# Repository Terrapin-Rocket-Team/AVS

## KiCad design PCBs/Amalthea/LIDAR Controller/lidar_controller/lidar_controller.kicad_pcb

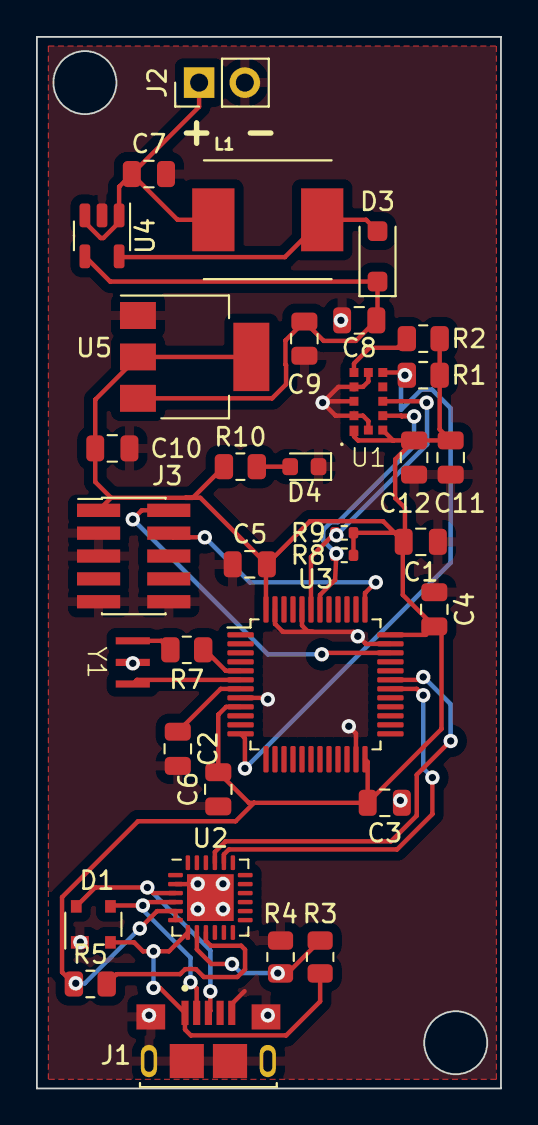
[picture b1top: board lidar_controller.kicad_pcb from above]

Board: 2 copper layers, 25.8 x 58.4 mm, 34 parts (0 on the bottom side), 23 nets.

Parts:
C1, C11: 4.7uF; C_0805_2012Metric
C2, C3, C4, C5, C6, C9, C12: 100nF; C_0805_2012Metric
C7, C8, C10: 10uF; C_0805_2012Metric
D1: SP0503BAHT; SOT-143
D3: D_Schottky; D_SOD-123F
D4: LED; D_0603_1608Metric
J1: 10118193-0001LF; AMPHENOL_10118193-0001LF
J2: Conn_01x02_Pin; PinHeader_1x02_P2.54mm_Vertical
J3: Conn_ARM_JTAG_SWD_10; PinHeader_2x05_P1.27mm_Vertical_SMD
L1: 10uH; IND_ASPI-0630LR-100M-T15
R1, R2: 10k; R_0805_2012Metric
R3: 22.1k; R_0805_2012Metric
R4: 47.5k; R_0805_2012Metric
R5: 1k; R_0805_2012Metric
R7: 1M; R_0805_2012Metric
R8, R9: 4.7k; R_0402_1005Metric
R10: 500; R_0805_2012Metric
U1: VL53L3CX
U2: CP2102N-Axx-xQFN24; QFN-24-1EP_4x4mm_P0.5mm_EP2.6x2.6mm
U3: STM32F103C8Tx; LQFP-48_7x7mm_P0.5mm
U4: RP400N501A-TR-FE; SOT-23-5
U5: LDL1117S33R; SOT-223
Y1: Resonator; JGC42-8828A_CSTNE10M0G550000R0

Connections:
+3V3: C1.2, C3.2, C4.2, C5.2, C6.2, C10.2, C11.2, C12.2, J3.1 (VTref), R1.1, R2.2, R5.1, R8.2, R9.2, R10.1, U1.1 (AVDDVCSEL), U1.11 (AVDD), U2.5 (VIO), U2.6 (VDD), U3.9 (VDDA), U3.24 (VDD), U3.36 (VDD), U3.48 (VDD), U5.2 (VOUT), U5.4 (VOUT)
+5V: C8.1, C9.1, D3.1 (K), U4.4 (VOUT), U5.3 (VIN)
/LIDAR/INT: R1.2, U1.7 (GPIO1), U3.12 (PA2)
/LIDAR/SCL: R8.1, U1.10 (SCL), U3.42 (PB6)
/LIDAR/SDA: R9.1, U1.9 (SDA), U3.43 (PB7)
/Regulator/VIN: C7.1, J2.1, L1.1, U4.1 (CE), U4.3 (VIN)
/STM32F103/M_RX: U2.21 (TXD), U3.31 (PA10)
/STM32F103/M_TX: U2.20 (RXD), U3.30 (PA9)
/STM32F103/SWCLK: J3.4 (SWDCLK/TCK), U3.37 (PA14)
/STM32F103/SWDIO: J3.2 (SWDIO/TMS), U3.34 (PA13)
GND: C1.1, C2.2, C3.1, C4.1, C5.1, C6.1, C7.2, C8.2, C9.2, C10.1, C11.1, C12.1, D1.1 (A), D4.1 (K), J1.5 (GND), J1.S1 (SHIELD), J1.S2 (SHIELD), J1.S3 (SHIELD), J1.S4 (SHIELD), J1.S5 (SHIELD), J1.S6 (SHIELD), J2.2, J3.3 (GND), J3.5 (GND), J3.9 (GNDDetect), J3.10 (~RESET), R4.1, U1.2 (AVSSVCSEL), U1.3 (GND), U1.4 (GND2), U1.6 (GND3), U1.12 (GND4), U2.2 (GND), U2.25 (GND), U3.8 (VSSA), U3.23 (VSS), U3.35 (VSS), U3.44 (BOOT0), U3.47 (VSS), U4.2 (GND), U5.1 (GND), Y1.2
unnamed: D3.2 (A), L1.2, U4.5 (LX)
unnamed: D4.2 (A), R10.2
unnamed: D1.4 (K), J1.3 (D+), U2.3 (D+)
unnamed: D1.3 (K), J1.2 (D-), U2.4 (D-)
unnamed: D1.2 (K), J1.1 (VUSB), R3.2, U2.7 (VREGIN)
unnamed: R7.2, Y1.1
unnamed: R2.1, U1.5 (XSHUT)
unnamed: R3.1, R4.2, U2.8 (VBUS)
unnamed: R5.2, U2.9 (~RST)
unnamed: C2.1, U3.7 (NRST)
unnamed: R7.1, U3.5 (PD0)
unnamed: U3.6 (PD1), Y1.3

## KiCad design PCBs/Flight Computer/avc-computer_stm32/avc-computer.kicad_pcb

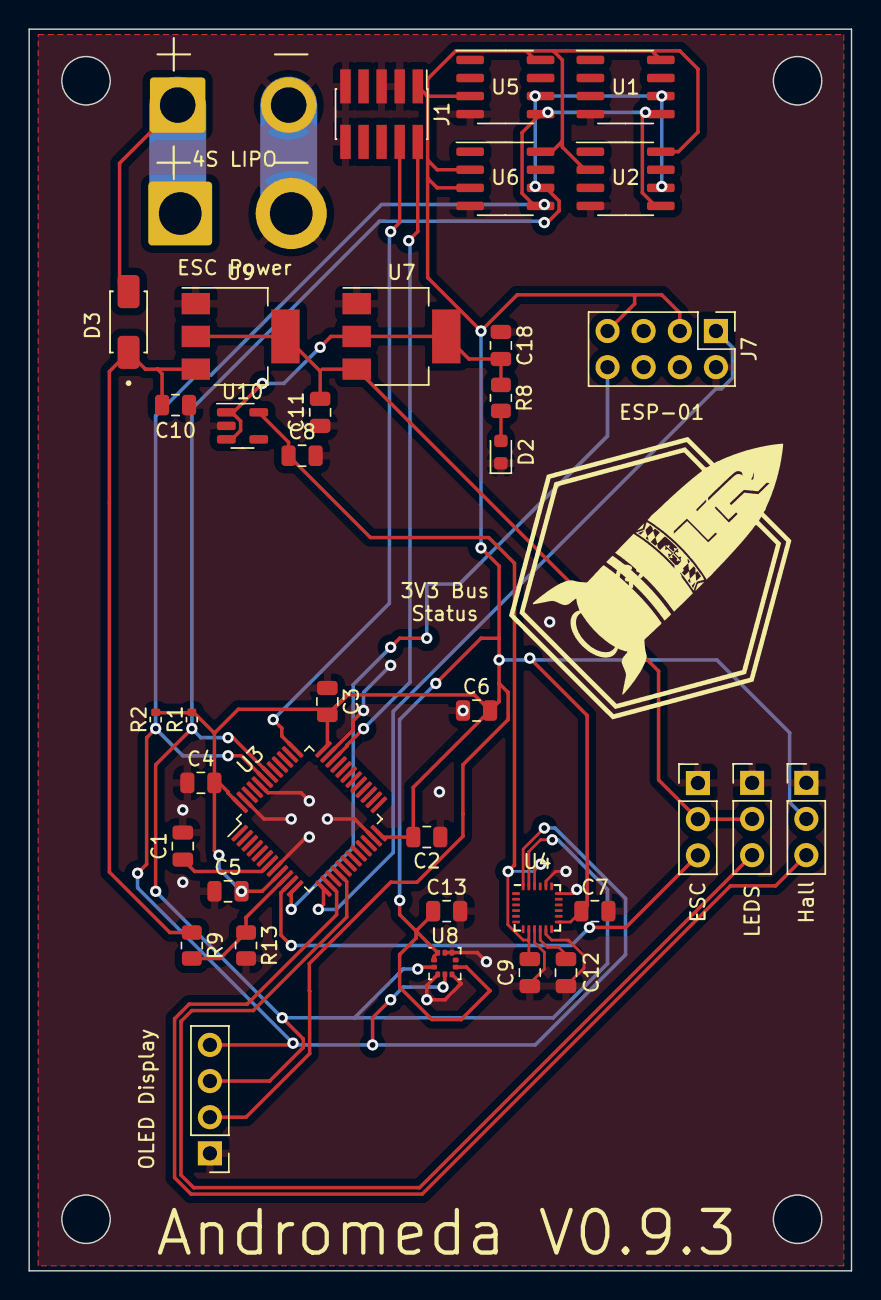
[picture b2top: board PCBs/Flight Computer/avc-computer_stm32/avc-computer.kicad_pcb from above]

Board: 2 copper layers, 57.8 x 87.2 mm, 39 parts (0 on the bottom side), 19 nets.

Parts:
C1, C2, C3, C4, C5, C13: 100nF; C_0805_2012Metric
C6, C11: 4.7uF; C_0805_2012Metric
C7, C8, C9, C12: 100nf; C_0805_2012Metric
C10, C18: 10uF; C_0805_2012Metric
D2: LED; D_0603_1608Metric
D3: D_Schottky; DIOM5226X230N
J1: Conn_ARM_JTAG_SWD_10; PinHeader_2x05_P1.27mm_Vertical_SMD
J2: Battery Connector; SolderWire-2sqmm_1x02_P7.8mm_D2mm_OD3.9mm
J3: Brake Servo Connector; PinHeader_1x03_P2.54mm_Vertical
J4: ESC Power; SolderWire-2sqmm_1x02_P7.8mm_D2mm_OD3.9mm
J5: ESC Connector; PinHeader_1x03_P2.54mm_Vertical
J6: OLED Display; PinHeader_1x04_P2.54mm_Vertical
J7: Conn_02x04_Odd_Even; PinHeader_2x04_P2.54mm_Vertical
J8: Hall Effect Sensor; PinHeader_1x03_P2.54mm_Vertical
R1, R2: 4.7k; R_0402_1005Metric
R8: 500; R_0805_2012Metric
R9: 1k; R_0805_2012Metric
R13: 200; R_0805_2012Metric
U1, U2, U5, U6: CAT24M01W; SOIC-8_3.9x4.9mm_P1.27mm
U3: STM32F103C8Tx; LQFP-48_7x7mm_P0.5mm
U4: InvenSense_QFN-24_3x3mm_P0.4mm
U7: LDL1117S33R; SOT-223
U8: LPS22HB; ST_HLGA-10_2x2mm_P0.5mm_LayoutBorder3x2y
U9: LDL1117S50R; SOT-223
U10: TLV70019_SOT23-5; SOT-23-5

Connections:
+3V3: C2.2, C3.2, C4.2, C5.2, C6.2, C7.1, C13.1, C18.2, J1.1 (VTref), J6.2, J7.3, J7.7, J8.2, R1.2, R2.2, R8.1, U1.8 (VCC), U2.2 (A1), U2.8 (VCC), U3.9 (VDDA), U3.24 (VDD), U3.36 (VDD), U3.48 (VDD), U4.13 (VDD), U5.3 (A2), U5.8 (VCC), U6.2 (A1), U6.3 (A2), U6.8 (VCC), U7.2 (VOUT), U7.4 (VOUT), U8.1 (Vdd_IO), U8.6 (~CS), U8.10 (VDD), U10.1 (IN), U10.3 (EN)
+5V: C11.2, J3.2, J5.2, U7.3 (VIN), U9.2 (VOUT), U9.4 (VOUT)
/1V9: C8.1, C9.2, U4.8 (VDDIO), U4.22 (nCS), U10.5 (OUT)
/Brake_Cont: J3.3, U3.16 (PA6)
/ESC_Cont: J5.3, U3.11 (PA1)
/HALL_OUTPUT: J8.3, U3.14 (PA4)
/Microcontroller/PA2: J7.8, U3.12 (PA2)
/Microcontroller/PA3: J7.1, U3.13 (PA3)
/Microcontroller/SWCLK: J1.4 (SWDCLK/TCK), U3.37 (PA14)
/Microcontroller/SWDIO: J1.2 (SWDIO/TMS), U3.34 (PA13)
/SCL: J6.3, R1.1, U1.6 (SCL), U2.6 (SCL), U3.42 (PB6), U4.23 (SCL/SCLK), U5.6 (SCL), U6.6 (SCL), U8.2 (SCL)
/SDA: J6.4, R2.1, U1.5 (SDA), U2.5 (SDA), U3.43 (PB7), U4.24 (SDA/SDI), U5.5 (SDA), U6.5 (SDA), U8.4 (SDA)
/VBAT: C10.2, D3.1 (K), R9.1, U9.3 (VIN)
GND: C1.2, C2.1, C3.1, C4.1, C5.1, C6.1, C7.2, C8.2, C9.1, C10.1, C11.1, C12.1, C13.2, C18.1, D2.1 (K), J1.3 (GND), J1.5 (GND), J1.9 (GNDDetect), J1.10 (~RESET), J2.2, J3.1, J4.2, J5.1, J6.1, J7.2, J8.1, R13.2, U1.4 (GND), U2.4 (GND), U3.8 (VSSA), U3.23 (VSS), U3.35 (VSS), U3.44 (BOOT0), U3.47 (VSS), U4.9 (AD0), U4.11 (FSYNC), U4.18 (GND), U4.20 (RESV), U5.4 (GND), U6.4 (GND), U7.1 (GND), U8.3 (RES), U8.5 (SA0), U8.8 (GND), U8.9 (GND), U9.1 (GND), U10.2 (GND)
unnamed: D2.2 (A), R8.2
unnamed: D3.2 (A), J2.1, J4.1
unnamed: C1.1, U3.7 (NRST)
unnamed: R9.2, R13.1, U3.10 (PA0)
unnamed: C12.2, U4.10 (REGOUT)

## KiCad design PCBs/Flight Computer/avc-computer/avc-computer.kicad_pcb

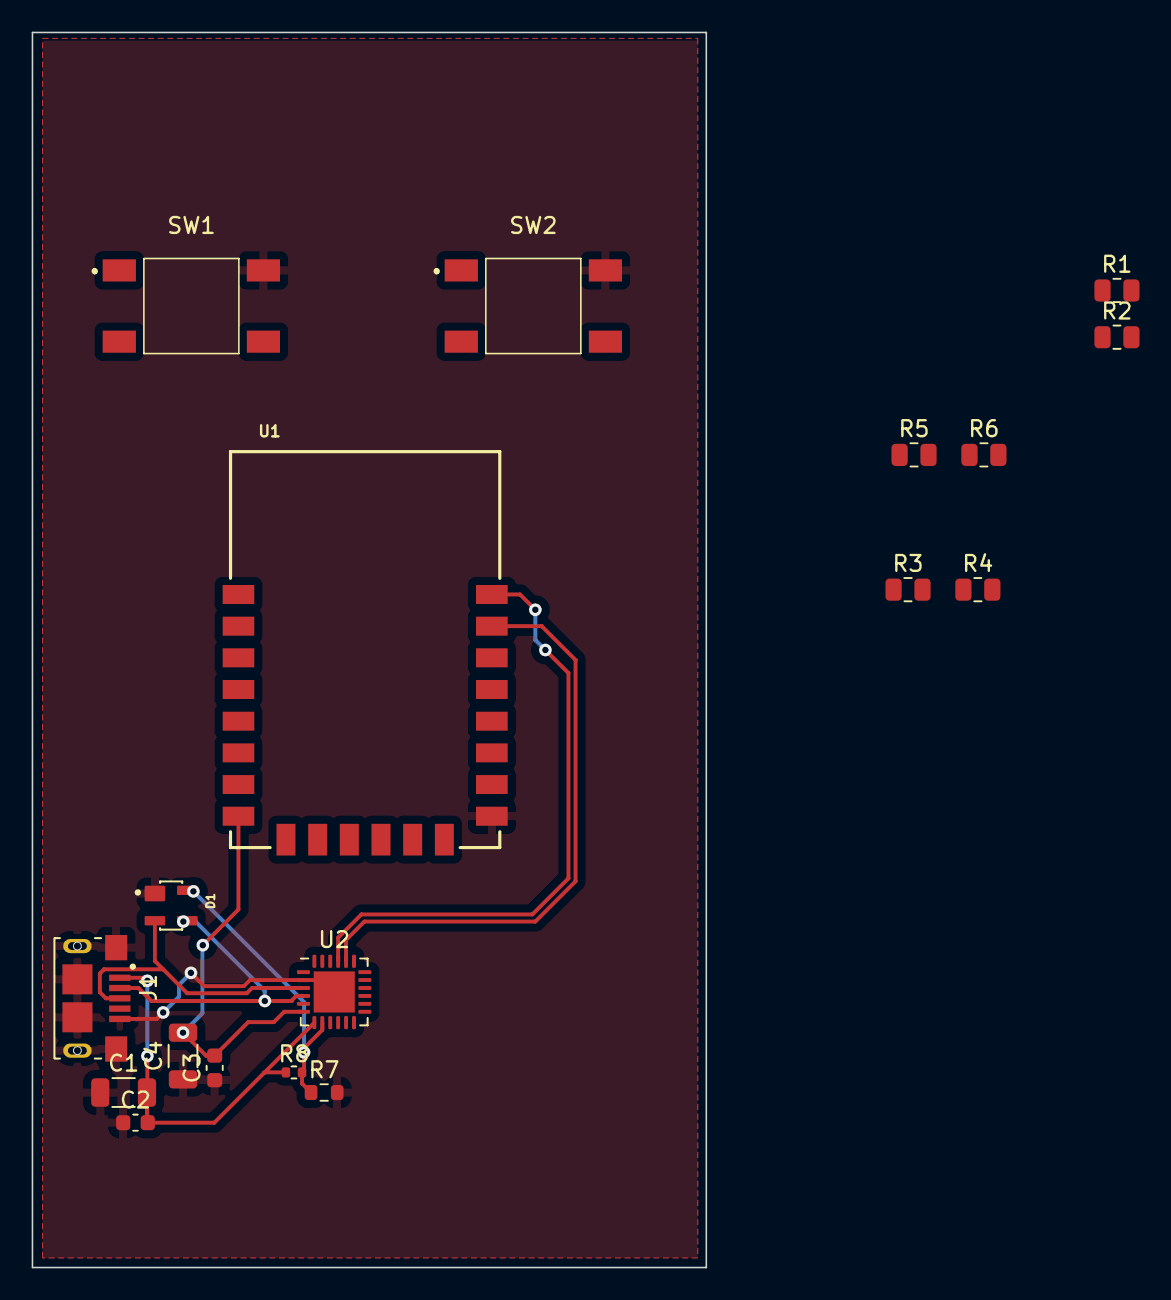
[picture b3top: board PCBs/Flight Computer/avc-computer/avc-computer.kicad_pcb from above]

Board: 2 copper layers, 42.5 x 78.0 mm, 18 parts (0 on the bottom side), 14 nets.

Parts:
C1, C4: 4.7uF; C_1206_3216Metric
C2, C3: 0.1uF; C_0603_1608Metric
D1: SP0503BAHTG; SOT143
J1: 10118193-0001LF; FCI_10118193-0001LF
R1, R2, R3, R4: 10k; R_0805_2012Metric
R5, R6: 4.7k; R_0805_2012Metric
R7: 47.5k; R_0603_1608Metric
R8: 22.1k; R_0402_1005Metric
SW1, SW2: SW_SPST; TL3301AF260QG
U1: ESP-12F
U2: CP2102N-Axx-xQFN24; QFN-24-1EP_4x4mm_P0.5mm_EP2.6x2.6mm

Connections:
+3V3: C3.2, C4.2, R1.2, R2.1, R4.1, R5.1, R6.1, U1.8 (VCC), U2.6 (VDD)
/Microcontroller/RX: U1.21 (RXD), U2.20 (RXD)
/Microcontroller/SCL: R6.2, U1.20 (GPIO5)
/Microcontroller/SDA: R5.2, U1.19 (GPIO4)
/Microcontroller/TX: U1.22 (TXD), U2.21 (TXD)
/USB/VREGIN: C1.2, C2.2, J1.1 (VUSB), R8.1, U2.7 (VREGIN)
GND: C1.1, C2.1, C3.1, C4.1, D1.1, J1.5 (GND), J1.S1 (SHIELD), J1.S2 (SHIELD), J1.S3 (SHIELD), J1.S4 (SHIELD), J1.S5 (SHIELD), J1.S6 (SHIELD), R3.2, R7.2, SW1.2 (B), SW2.2 (B), U1.15 (GND), U2.2 (GND), U2.25 (GND)
unnamed: D1.2, J1.3 (D+), U2.3 (D+)
unnamed: D1.3, J1.2 (D-), U2.4 (D-)
unnamed: D1.4, R7.1, R8.2, U2.8 (VBUS)
unnamed: R1.1, U1.3 (EN)
unnamed: R2.2, SW1.1 (A), U1.1 (RST)
unnamed: R3.1, U1.16 (GPIO15)
unnamed: R4.2, SW2.1 (A), U1.18 (GPIO0)

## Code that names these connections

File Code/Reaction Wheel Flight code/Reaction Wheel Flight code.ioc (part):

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Mcu.Name=STM32F103C(8-B)Tx
Mcu.Package=LQFP48
Mcu.UserName=STM32F103C8Tx
PA1.Signal=S_TIM2_CH2
PA6.Signal=S_TIM3_CH1
PB6.Mode=I2C
PB6.Signal=I2C1_SCL
PB7.Mode=I2C
PB7.Signal=I2C1_SDA
RCC.SYSCLKFreq_VALUE=64000000
RCC.SYSCLKSource=RCC_SYSCLKSOURCE_PLLCLK
board=custom

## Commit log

2023-06-06 Fixed all issues except for 5v buck inductor heating
2023-07-26 Renamed folder
2023-07-26 Addded gerber files for 0.9.1
2023-07-26 Began fixing reference designators
2023-07-26 Relpaced swithcing regulator with linear regulator. Removed unneccesary components. Replaced barometric pressure sensor with better one. Added connectors for brake servo & hall effect sensor
2023-09-07 Added matlab script for rcs thruster calcs
2023-09-13 Updated matlab script with corrected equations
2023-09-14 Updated exit velocity calc
2023-09-18 Optimize for sea level
2023-10-15 Started writing code for characterizing PWM range for motor & controller
2023-11-12 Replaced IMU and added 1.9v bus
2023-12-07 Created lidar test pcb
